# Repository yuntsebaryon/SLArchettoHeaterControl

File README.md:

SLArchetto Heater Control
=========================

### Gas heater control: 2023.5.15

- Solid state relay status:
    - close the circuit: the heater power on, the light is on, and the relay status is 1 (true)
    - open the circuit: the heater power off the light is off, and the relay status is 0 (false)
- The `relay status` is defined in the arduino code, `ArduinoCode/GasHeaterControl/GasHeaterControl.ino`
- Documents for EEIP review in the [google drive](https://drive.google.com/drive/folders/1yJYlNlNA7SNpJz1zEHQmS_Y9HfFr7dbM?usp=sharing)

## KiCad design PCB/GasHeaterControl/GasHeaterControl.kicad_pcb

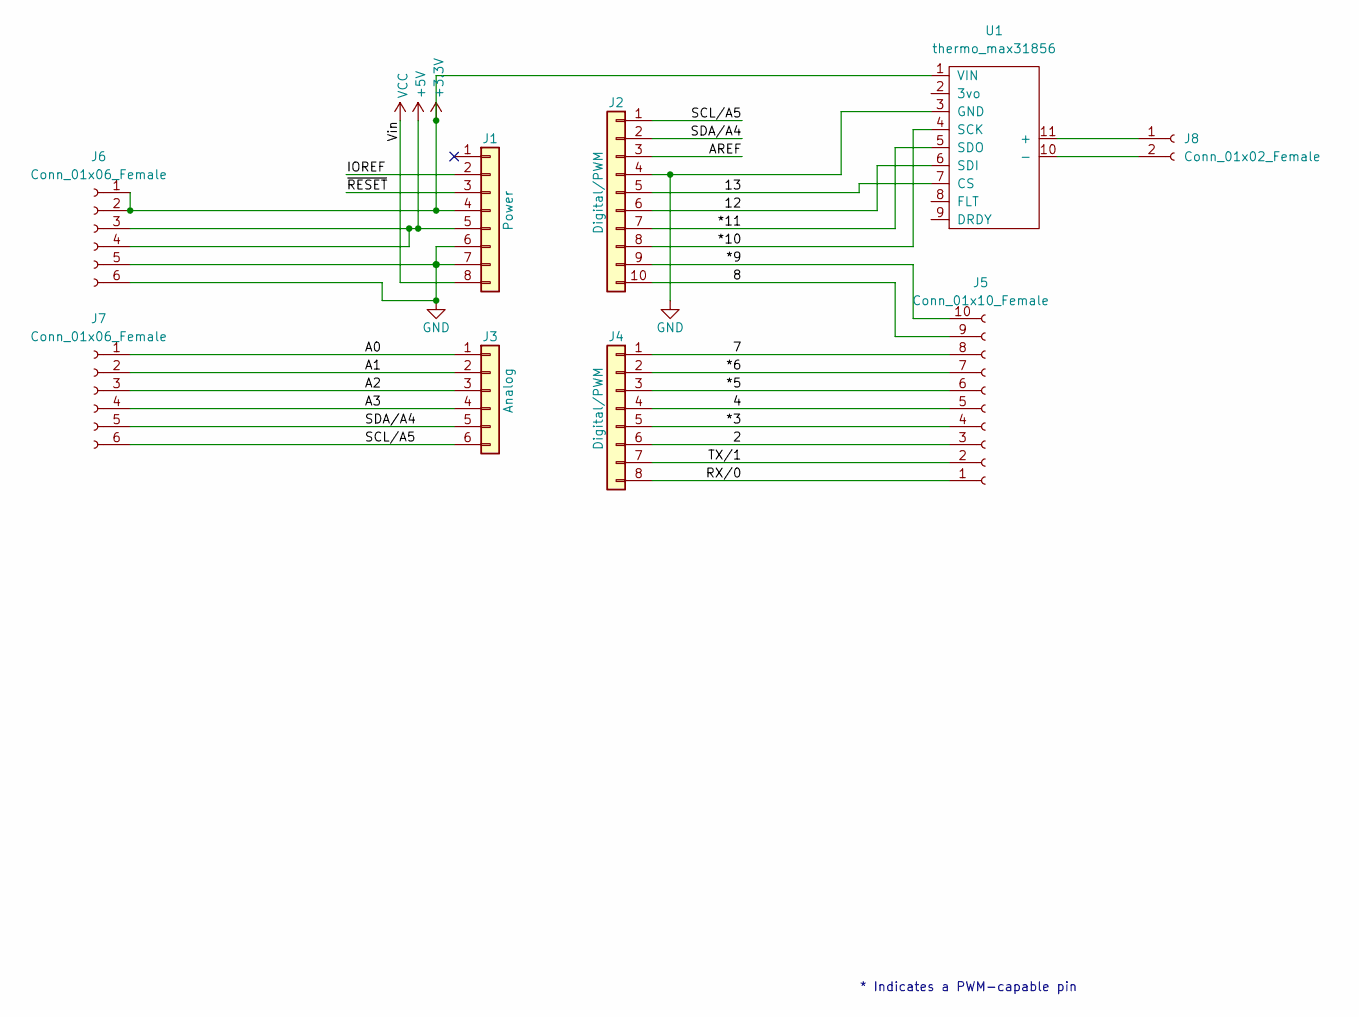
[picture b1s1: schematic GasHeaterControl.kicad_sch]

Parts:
J1: Power; PinSocket_1x08_P2.54mm_Vertical
J2: Digital/PWM; PinSocket_1x10_P2.54mm_Vertical
J3: Analog; PinSocket_1x06_P2.54mm_Vertical
J4: Digital/PWM; PinSocket_1x08_P2.54mm_Vertical
J5: Conn_01x10_Female; PhoenixContact_MCV_1,5_10-G-3.5_1x10_P3.50mm_Vertical
J6, J7: Conn_01x06_Female; PhoenixContact_MCV_1,5_6-G-3.5_1x06_P3.50mm_Vertical
J8: Conn_01x02_Female; PhoenixContact_MCV_1,5_2-G-3.5_1x02_P3.50mm_Vertical
U1: thermo_max31856; MAX31856

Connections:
+3V3: J1.4, J6.1, J6.2, U1.1 (VIN)
+5V: J1.5, J6.3, J6.4
/2: J4.6, J5.3
/4: J4.4, J5.5
/7: J4.1, J5.8
/8: J2.10, J5.9
/12: J2.6, U1.6 (SDI)
/13: J2.5, U1.7 (CS)
/*3: J4.5, J5.4
/*5: J4.3, J5.6
/*6: J4.2, J5.7
/*9: J2.9, J5.10
/*10: J2.8, U1.4 (SCK)
/*11: J2.7, U1.5 (SDO)
/A0: J3.1, J7.1
/A1: J3.2, J7.2
/A2: J3.3, J7.3
/A3: J3.4, J7.4
/AREF: J2.3
/IOREF: J1.2
/RX/0: J4.8, J5.1
/SCL/A5: J2.1, J3.6, J7.6
/SDA/A4: J2.2, J3.5, J7.5
/TX/1: J4.7, J5.2
/~RESET: J1.3
GND: J1.6, J1.7, J2.4, J6.5, J6.6, U1.3 (GND)
unnamed: J8.2, U1.10 (-)
unnamed: J8.1, U1.11 (+)
VCC: J1.8

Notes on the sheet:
* Indicates a PWM-capable pin

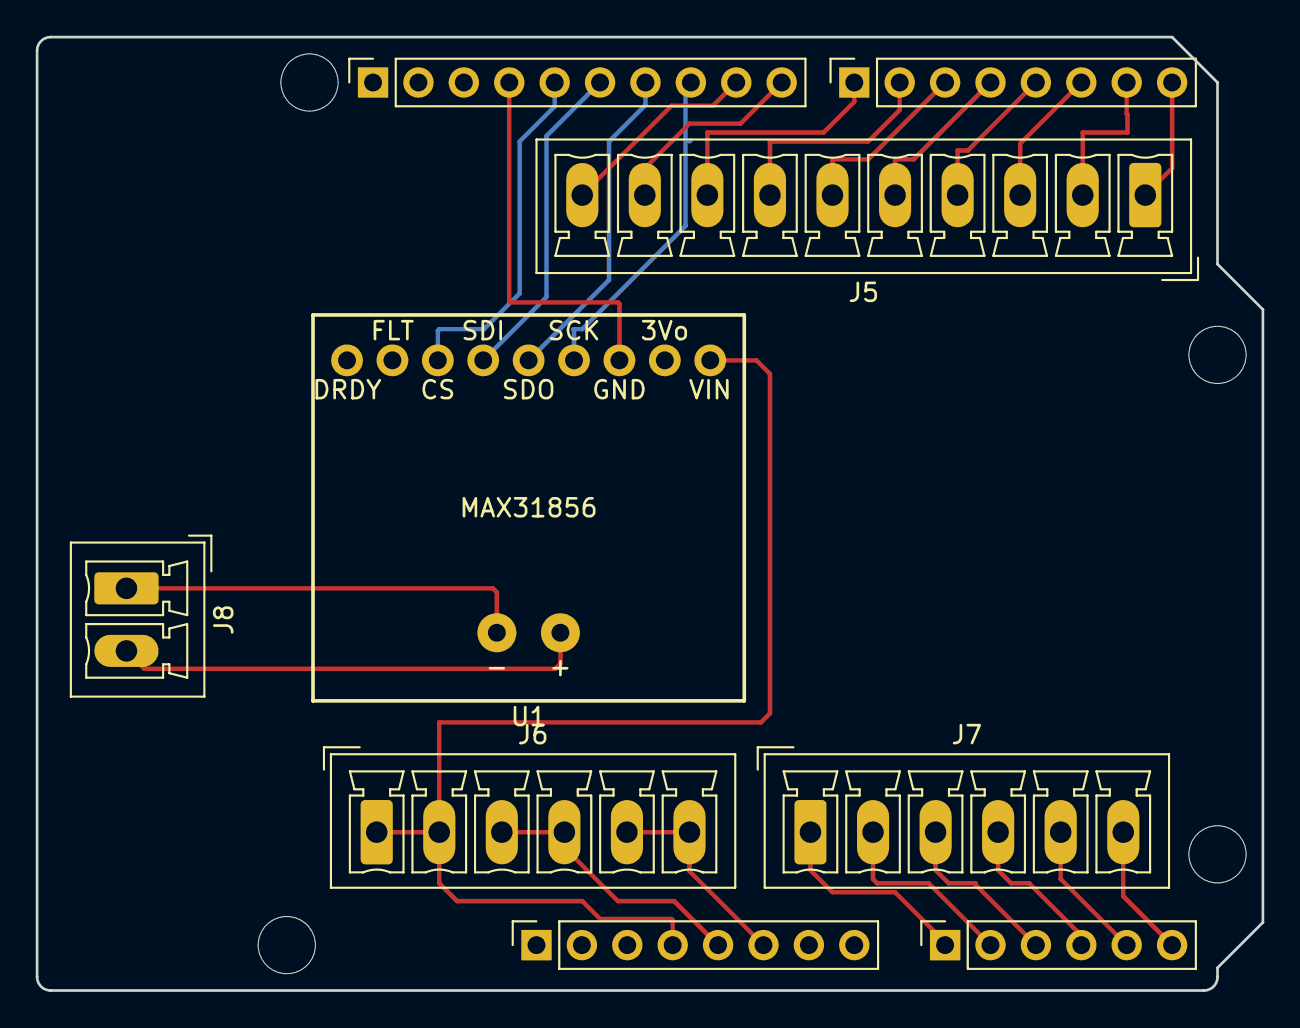
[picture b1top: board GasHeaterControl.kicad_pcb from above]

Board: 2 copper layers, 68.6 x 53.3 mm, 13 parts (0 on the bottom side), 25 nets.

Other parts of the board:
MH1, MH2, MH3, MH4: MountingHole_3.2mm

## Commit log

2022-11-20 .gitignore
2022-11-20 organized the directory
2022-11-20 reorganize the folder
2022-11-20 change the output pdf file
2022-11-30 gas heater control schematic
2022-12-06 initiate the configuration of the pinmode
2022-12-06 footprint in pdf
2022-12-07 Code to test TC readout
2022-12-08 correct the digital output pin
2022-12-09 working version of the code!
2022-12-09 Code without ethernet
2023-05-06 add the update
2023-05-16 updates on README and the schematics
2023-05-16 add the google drive for EEIP review
